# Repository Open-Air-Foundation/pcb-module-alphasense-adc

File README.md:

# AirGradient AlphaSense ADC Module — Hardware

> KiCad hardware design files for the AirGradient AlphaSense ADC module — the interface board that digitizes the AlphaSense electrochemical gas sensors in the [Open Air Max](https://www.airgradient.com/professional/products/open-air-max/) outdoor air quality monitor.

## Overview

A compact 2-layer board carrying two Texas Instruments ADS1115 16-bit ADCs that read the AlphaSense electrochemical sensors — NO₂ (A43F) and O₃ (A431) — and report to the host monitor over I²C. The supply is filtered through a ferrite bead for clean analog readings.

## Design structure

A single KiCad project in `alphasense-adc/`: one schematic sheet and a 2-layer board. (The project was originally named "ADS1115 for AlphaSense NO2-O3", published on Bitbucket as `alphasense-oa-pcb`, and renamed `alphasense-adc` here; the Gerber filenames inside the archived production zip keep the `alphasense-oa-pcb` naming.)

## Repository structure

```
alphasense-adc/           # KiCad project (schematic + board), production/
libraries/                   # Bundled 3D model libraries
```

## Key components

| Function | Part | Ref |
|---|---|---|
| 16-bit I²C ADC | TI ADS1115IDGSR | U1–U2 |
| Supply filter (ferrite bead) | MMZ2012Y152BT000 | FB1 |
| Host connector (1.25 mm, 8-pin) | Molex 53261-0871 | J1, CN1 |
| Sensor header (2×5 IDC, 2.54 mm) | AWHW2-10G | J2 |

## Toolchain

- **KiCad 9** (file format 2024-12). Symbols and footprints are embedded in the design files; bundled 3D models are referenced project-relative — the project opens without any extra library setup.
- **[Fabrication Toolkit](https://github.com/bennymeg/Fabrication-Toolkit)** plugin — generates the Gerber/BOM/CPL production set in JLCPCB-compatible format.
- Active DRC rules are in `alphasense-adc/alphasense-adc.kicad_dru`.

## Fabrication

`alphasense-adc/production/` holds the ready-to-order set: Gerber zip, BOM, designators, and pick-and-place positions (generated with Fabrication Toolkit, LCSC part numbers for assembly at JLCPCB).

## Versioning & releases

Hardware revisions are tagged on this repository. Per-version release notes and the matching production file set are published on the [GitHub Releases](../../releases) page.

## License

This is open-source hardware. The design files in this repository are licensed under the
[Creative Commons Attribution-ShareAlike 4.0 International (CC BY-SA 4.0)](https://creativecommons.org/licenses/by-sa/4.0/) license — see [LICENSE](LICENSE).

You are free to use, modify, and manufacture these designs, including commercially, provided you credit AirGradient and share derivative designs under the same license.

## Maintainers

AirGradient hardware team.

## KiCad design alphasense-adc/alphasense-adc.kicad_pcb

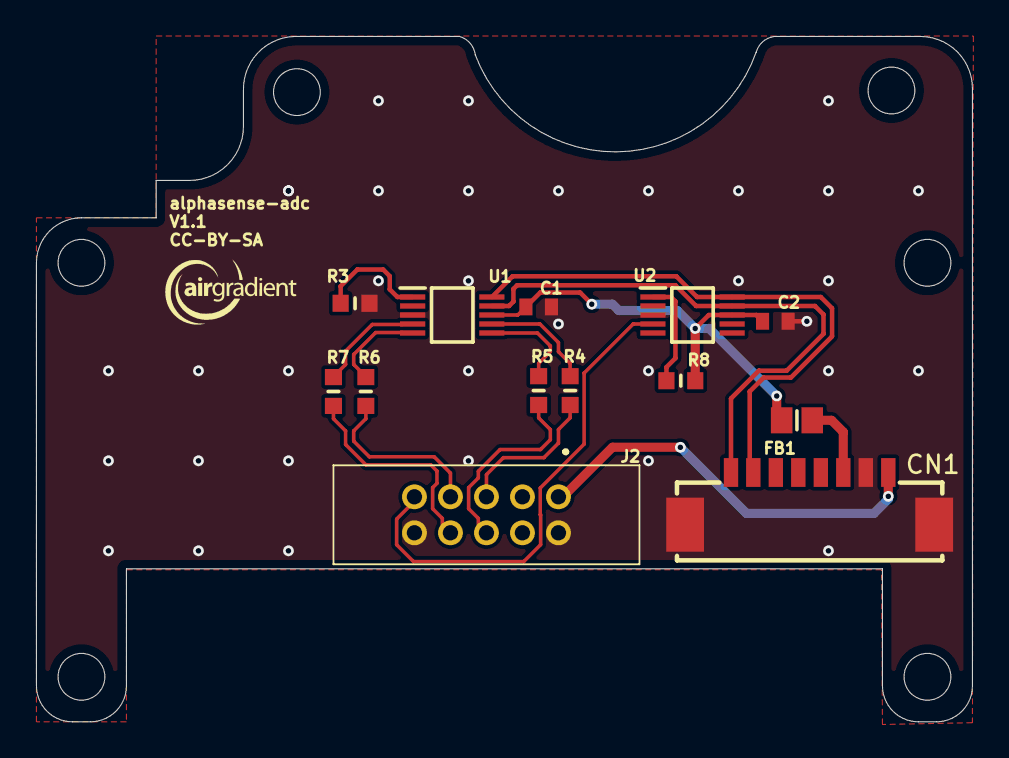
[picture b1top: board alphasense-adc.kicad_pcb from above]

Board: 2 copper layers, 52.0 x 38.1 mm, 13 parts (0 on the bottom side), 17 nets.

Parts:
C1, C2: CL10B105KP8NNNC; CAPC1608X90N
CN1: 532610871; CONN-SMD_532610871
FB1: MMZ2012Y152BT000; BEADC2012X105N
J2: AWHW2-10G-0202-T-R; AWHW210G0202TR
R3, R8: 10K; RESC1608X55N
R4, R5, R6, R7: 1K; RESC1608X55N
U1, U2: ADS1115IDGSR; SOP50P490X110-10N

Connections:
3V3: C1.1, C2.1, FB1.2, R8.1, U1.8 (VDD), U2.8 (VDD)
5V: CN1.8, J2.1
+3.3V: CN1.6, FB1.1
/PT1000: J2.9, U2.4 (AIN0)
/SCL: CN1.2, U1.10 (SCL), U2.10 (SCL)
/SDA: CN1.1, U1.9 (SDA), U2.9 (SDA)
/SN1+: J2.8, R7.2
/SN1-: J2.7, R6.2
/SN1_N: R6.1, U1.5 (AIN1)
/SN1_P: R7.1, U1.4 (AIN0)
/SN2+: J2.6, R5.1
/SN2-: J2.5, R4.2
/SN2_N: R4.1, U1.7 (AIN3)
/SN2_P: R5.2, U1.6 (AIN2)
GND: C1.2, C2.2, CN1.0, CN1.7, J2.2, J2.10, R3.2, U1.3 (GND), U2.3 (GND)
unnamed: R3.1, U1.1 (ADDR)
unnamed: R8.2, U2.1 (ADDR)

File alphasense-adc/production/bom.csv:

Designator,Footprint,Quantity,Value,LCSC Part #
"C1, C2",CAPC1608X90N,2,CL10B105KP8NNNC,
CN1,CONN-SMD_532610871,1,532610871,C293349
FB1,BEADC2012X105N,1,MMZ2012Y152BT000,
J2,AWHW210G0202TR,1,AWHW2-10G-0202-T-R,
"R3, R8",RESC1608X55N,2,10K,
"R4, R5, R6, R7",RESC1608X55N,4,1K,
"U1, U2",SOP50P490X110-10N,2,ADS1115IDGSR,
